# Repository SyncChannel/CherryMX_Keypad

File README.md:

# CherryMX_Keypad
An open-source, Arduino-compatible Cherry MX keypad!

Link to blog post:

http://syncchannel.blogspot.com/2016/06/cherry-mx-keypad.html

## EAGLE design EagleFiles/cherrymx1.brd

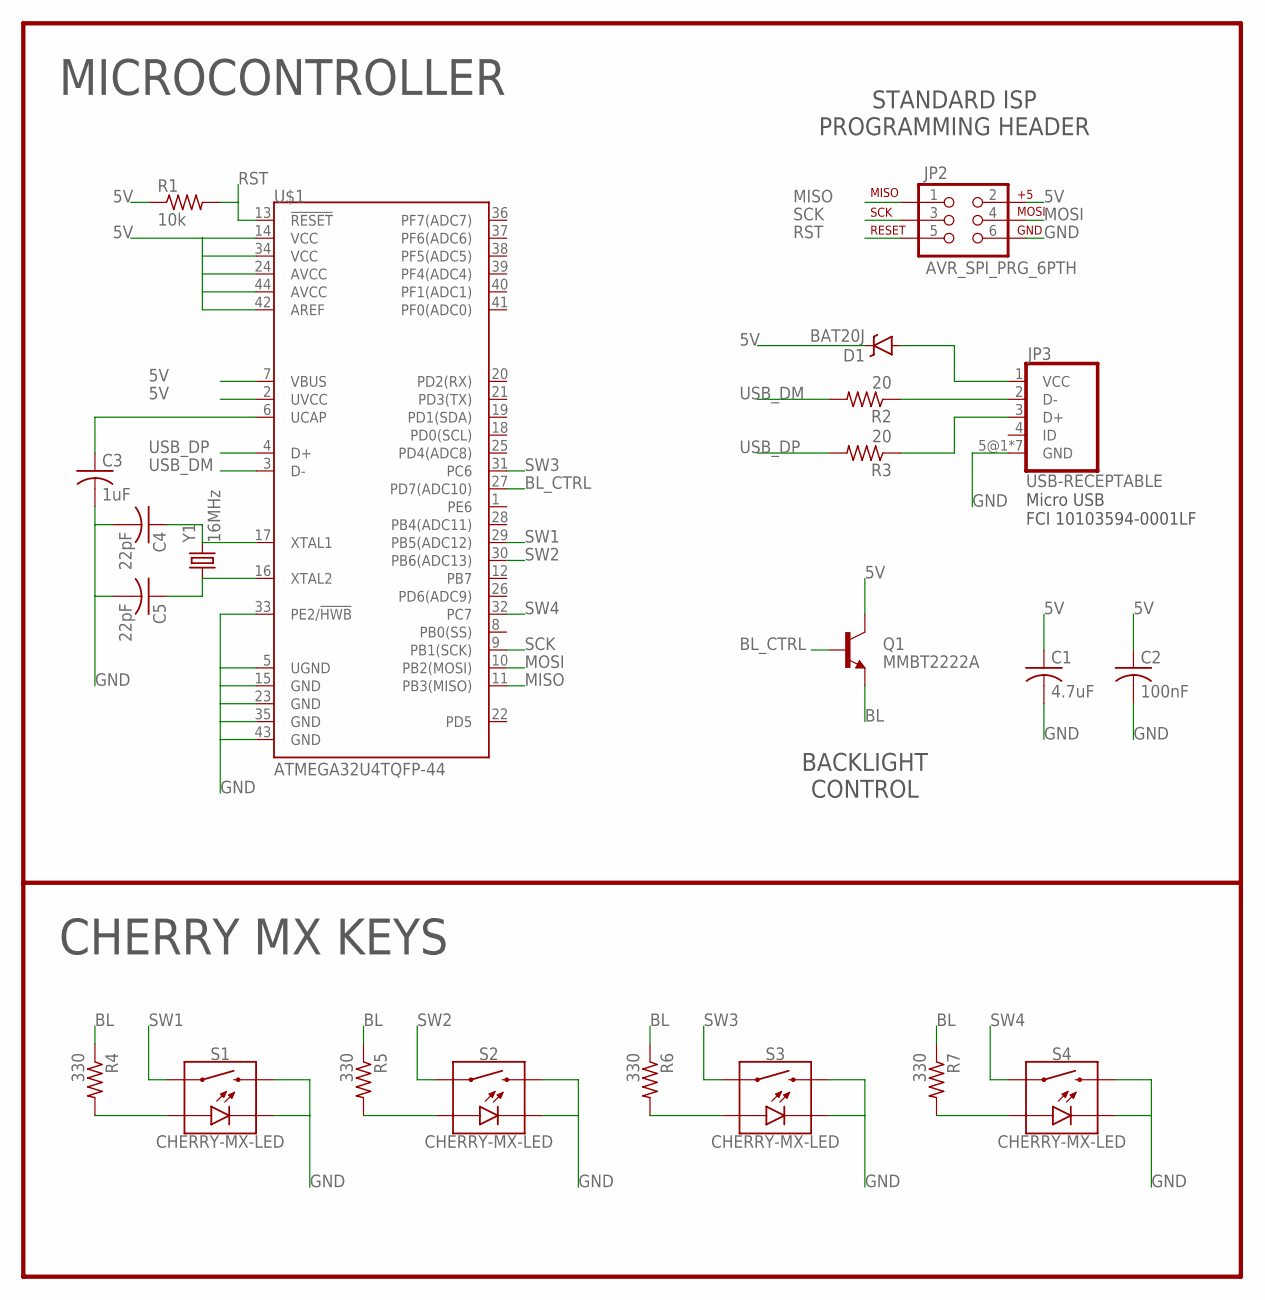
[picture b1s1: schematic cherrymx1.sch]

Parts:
C1: 4.7uF; C0603
C2: 100nF; C0603
C3: 1uF; C0603
C4, C5: 22pF; C0603
D1: BAT20J; SOD-323
JP2: AVR_SPI_PRG_6PTH; 2X3
JP3: USB-RECEPTABLE; FCI-10103594-0001LF
Q1: MMBT2222A; SOT23-3
R1: 10k; R0603
R2, R3: 20; R0603
R4, R5, R6, R7: 330; R0603
S1, S2, S3, S4: CHERRY-MX-LED
U$1: ATMEGA32U4TQFP-44; TQFP44
Y1: 16MHz; CRYSTAL-SMD-5X3

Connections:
5V: C1.1, C2.1, D1.C, JP2.2, Q1.3 (C), R1.1, U$1.2 (UVCC), U$1.7 (VBUS), U$1.14 (VCC), U$1.24 (AVCC), U$1.34 (VCC), U$1.42 (AREF), U$1.44 (AVCC)
BL: Q1.2 (E), R4.1, R5.1, R6.1, R7.1
BL_CTRL: Q1.1 (B), U$1.27 (PD7(ADC10))
GND: C1.2, C2.2, C3.2, C4.2, C5.2, JP2.6, JP3.5@1 (GND), JP3.5@2 (GND), JP3.5@3 (GND), JP3.5@4 (GND), JP3.5@5 (GND), JP3.5@6 (GND), JP3.5@7 (GND), S1.K (C), S1.S2, S2.K (C), S2.S2, S3.K (C), S3.S2, S4.K (C), S4.S2, U$1.5 (UGND), U$1.15 (GND), U$1.23 (GND), U$1.33 (PE2/!HWB), U$1.35 (GND), U$1.43 (GND)
MISO: JP2.1, U$1.11 (PB3(MISO))
MOSI: JP2.4, U$1.10 (PB2(MOSI))
unnamed: D1.A, JP3.1 (VCC)
unnamed: JP3.2 (D-), R2.1
unnamed: JP3.3 (D+), R3.1
unnamed: C3.1, U$1.6 (UCAP)
unnamed: C4.1, U$1.17 (XTAL1), Y1.3 (2)
unnamed: C5.1, U$1.16 (XTAL2), Y1.1
unnamed: R4.2, S1.A
unnamed: R6.2, S3.A
unnamed: R7.2, S4.A
unnamed: R5.2, S2.A
RST: JP2.5, R1.2, U$1.13 (!RESET)
SCK: JP2.3, U$1.9 (PB1(SCK))
SW1: S1.S1, U$1.29 (PB5(ADC12))
SW2: S2.S1, U$1.30 (PB6(ADC13))
SW3: S3.S1, U$1.31 (PC6)
SW4: S4.S1, U$1.32 (PC7)
USB_DM: R2.2, U$1.3 (D-)
USB_DP: R3.2, U$1.4 (D+)

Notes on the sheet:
Micro USB FCI 10103594-0001LF
MICROCONTROLLER
CHERRY MX KEYS
BACKLIGHT CONTROL
STANDARD ISP PROGRAMMING HEADER

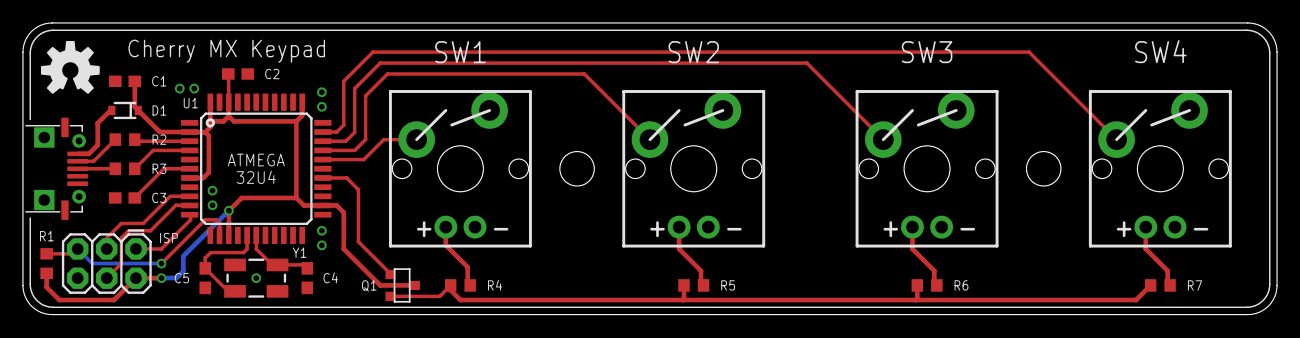
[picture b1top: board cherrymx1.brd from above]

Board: 2 copper layers, 109.2 x 25.4 mm, 23 parts (0 on the bottom side), 24 nets.

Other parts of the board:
U$2: OSHW-LOGO-M

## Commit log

2016-06-04 :octocat: Added .gitattributes & .gitignore files
2016-06-04 Added design files
2016-06-05 Added readme

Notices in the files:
parts and their libraries:
SparkFun-Electromechanical2: Licensing: Creative Commons ShareAlike 4.0 International - https://creativecommons.org/licenses/by-sa/4.0
